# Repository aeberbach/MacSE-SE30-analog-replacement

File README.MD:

# Analog board replacement, including power supply, for Mac SE or SE/30.

This project does not solve the problem of video. It's here because some people expressed an interest in having it as is. I'm working on a complimentary project that plugs into J2 of this board and will convert video to a LCD display, allowing the Mac to look like nothing is changed... except that the display is mysteriously flat, and very sharp, and it doesn't get hot any more.

The PSU board mounts a Mean Well PT-65B power supply module that meets most of the Mac's needs. The -5V supply is provided by an additional 7905 linear regulator. The schematic is extremely simple - a rotary encoder routed to header J2, a fan header, and apart from that the PCB is mostly physical support. Connectors are placed so that it should be no trouble plugging the original Mac drive power and logic board cables into this board.

This power supply is not quite as beefy as the original Mac PSU. But it's not 30 years old and you're not powering a 1980s hard drive or a CRT any more. From what I have measured I think it's enough.

The 3D printed parts are designed so that no supports are needed just because I hate removing supports. The spacer plate is required because the sheet steel of the Mac chassis needs to go up between the PSU and the PCB. Making the spacer a separate part simplifies the print. The main piece should be obvious - a fan inserts into it with sides open, allowing the use of a 60mm fan while retaining the original PSU width. It is held in place with the lid.

With this board in place your Mac will run happily but of course will not show anything, that part is up to you at this point. If you do start playing with video out the first thing you _might_ need to do is use a 5V-tolerant buffer/level shifter - most FPGAs would like to see a maximum 3.3V on that video signal.

The fan may not be required in the final version. When it is finished I can close everything up with a measuring device inside to monitor temperatures in various places. If the fan is required I will 3D print a kind of funnel directing the exhaust from the PSU enclosure up and out of the existing case fan hole. If not required I'll just print a blank to go in place of the fan or revise the shroud design to leave the fan out.

I did not find a rotary encoder that was tall enough to just fit. You need to exercise your own ingenuity there, I used a mezzanine PCB and raised the encoder on some pins. The plane that the encoder's pins should lie on is marked on the PCB assuming you use the encoder in the datasheets folder. If you get it in just the right place you can keep the original Mac brightness knob! The encoder can act as a brightness control of sorts varying the light color of the video, or altering the PWM duty cycle of your LCD backlight. 

Unless you are used crimping connectors to make up cables correctly and you can safely wire up power supply modules like this don't do it. This could easily destroy your Mac or kill you with a simple mistake.

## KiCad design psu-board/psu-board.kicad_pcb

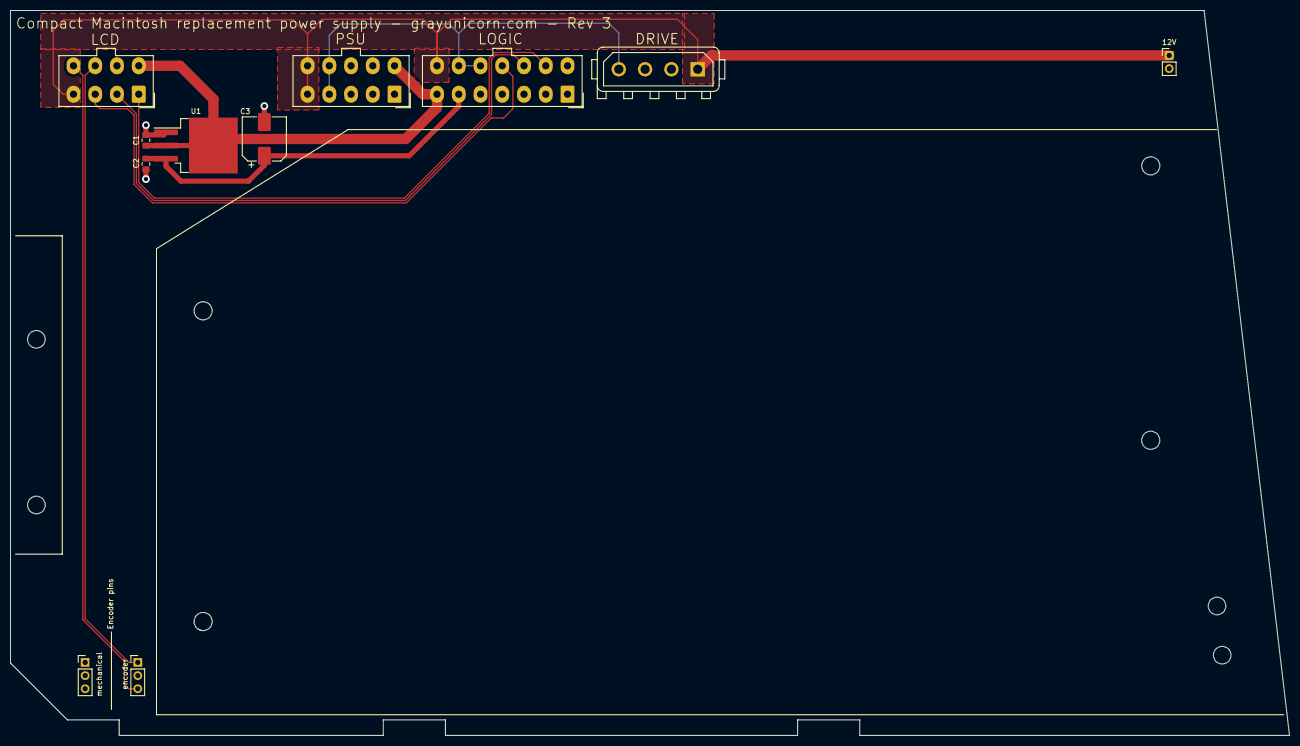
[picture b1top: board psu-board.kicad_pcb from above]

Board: 2 copper layers, 247.0 x 140.0 mm, 11 parts (0 on the bottom side), 8 nets.

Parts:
C1: 2.2uF; C_0805_2012Metric_Pad1.18x1.45mm_HandSolder
C2: 1uF; C_0805_2012Metric_Pad1.18x1.45mm_HandSolder
C3: 220uF 16V; CP_Elec_8x10
J1: Conn_02x05_Top_Bottom; Molex_Mini-Fit_Jr_5566-10A_2x05_P4.20mm_Vertical
J2: Conn_02x04_Top_Bottom; Molex_Mini-Fit_Jr_5566-08A_2x04_P4.20mm_Vertical
J3: Conn_01x02; PinHeader_1x02_P2.54mm_Vertical
J4: Conn_01x04; TE_MATE-N-LOK_350211-1_1x04_P5.08mm_Vertical
J5: Logic board connector; Molex_Mini-Fit_Jr_5566-14A_2x07_P4.20mm_Vertical
SW1, SW1#2: Rotary_Encoder; PinHeader_1x03_P2.54mm_Vertical
U1: MC7905; TO-263-3_TabPin2

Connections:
/5V: J1.4, J1.9, J4.4, J5.12, J5.13
/12V: J1.5, J1.10, J2.4, J3.1, J4.1, J5.14
/-5V: C2.2, C3.1, J5.6, U1.3
/-12V: C1.2, J1.6, J2.5, J5.7, U1.2
/GND: C1.1, C2.1, C3.2, J1.1, J1.2, J1.3, J1.7, J1.8, J2.6, J3.2, J4.2, J4.3, J5.1, J5.2, J5.3, J5.4, J5.5, J5.8, U1.1
/HSYNC: J2.2, J5.10
/VIDEO: J2.1, J5.9
/VSYNC: J2.3, J5.11

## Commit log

2021-08-31 Split this part off into a new repo
2021-08-31 readme
2021-08-31 typos
2021-08-31 more typos
2021-08-31 typos ahoy
2021-08-31 an endless sea of typos
2021-08-31 got to be the last one
